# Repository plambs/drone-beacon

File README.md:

# Drone beacon

## Description

This repository contain the source code and schematic of the drone beacon that is mandatory for all flying models over 800gr in France.
The beacon use a ESP32 to send the model id over wifi and a gps module to know it position.

All model must be registered on [AlphaTango](https://alphatango.aviation-civile.gouv.fr/login.jsp)

This work is based on the work done by Arnaud Mazin and the source of it can be found [here](https://www.club-modelisme-saclay.fr/ameliorations-balise-signalement-electronique-modeles-reduits-volants/)

## Build, flash and monitor

### Install ESP-IDF tools

Follow the [get-started](https://docs.espressif.com/projects/esp-idf/en/stable/esp32/get-started/linux-macos-setup.html) of the ESP IDF tools documentation.

For linux users
```
sudo apt-get install git wget flex bison gperf python3 python3-pip python3-venv cmake ninja-build ccache libffi-dev libssl-dev dfu-util libusb-1.0-0

mkdir -p ~/esp
cd ~/esp
git clone -b v5.4.3 --recursive https://github.com/espressif/esp-idf.git

cd ~/esp/esp-idf
./install.sh esp32
```

After that when you want to use the ESP-IDF tools you only need to source the export.sh script.
```
. $HOME/esp/esp-idf/export.sh
```

### Init submodule

```
git submodule update --init --recursive
```

### Beacon

```
cd sources/beacon
idf.py build
idf.py flash
```

Balise status code
|Status|Fast blink|Slow blink|
|---|---|---|
|Reset GPS|4||
|No position|3||
|Position but no home (not enough precision)|2||
|Trasmiting beacon (beacon is working)||1|

Initialisation time take at least 2 minute in ideal condition

### Receiver

```
cd sources/receiver
idf.py build
idf.py flash
```

### Monitor the serial output

```
idf.py monitor
```
To exit the monitor use Ctrl+T Ctrl+X

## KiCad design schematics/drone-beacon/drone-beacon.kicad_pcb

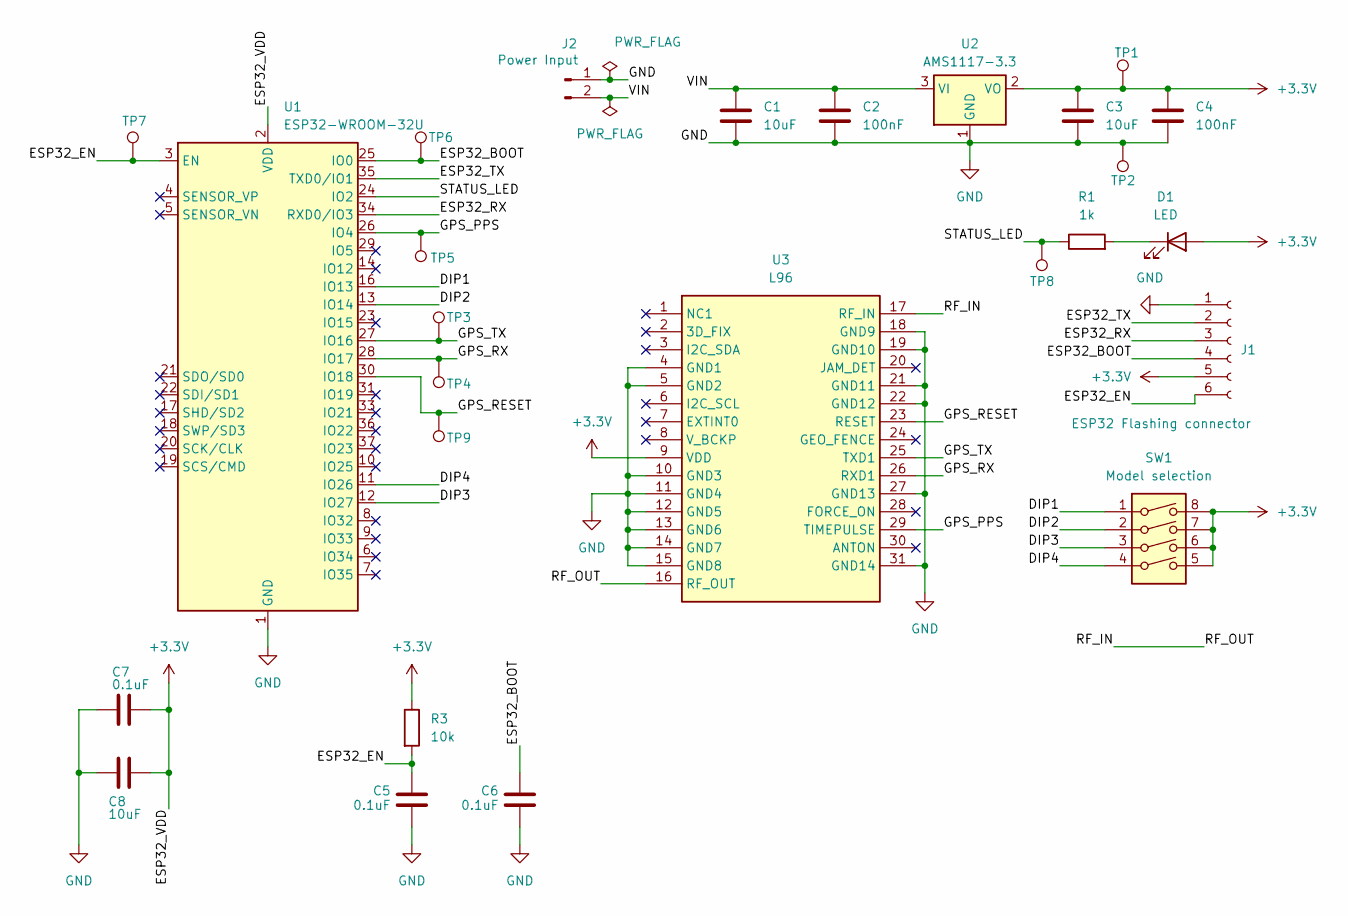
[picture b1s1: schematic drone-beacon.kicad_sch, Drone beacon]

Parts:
C1, C3, C8: 10uF; C_0402_1005Metric_Pad0.74x0.62mm_HandSolder
C2, C4: 100nF; C_0402_1005Metric_Pad0.74x0.62mm_HandSolder
C5, C6, C7: 0.1uF; C_0402_1005Metric_Pad0.74x0.62mm_HandSolder
D1: LED; LED_0402_1005Metric_Pad0.77x0.64mm_HandSolder
J1: ESP32 Flashing connector; JST_SHL_SM06B-SHLS-TF_1x06-1MP_P1.00mm_Horizontal
J2: Power Input; PinHeader_1x02_P2.00mm_Vertical
R1: 1k; R_0402_1005Metric_Pad0.72x0.64mm_HandSolder
R3: 10k; R_0402_1005Metric_Pad0.72x0.64mm_HandSolder
SW1: Model selection; SW_DIP_SPSTx04_Slide_Copal_CHS-04B_W7.62mm_P1.27mm
TP1, TP2, TP3, TP4, TP5, TP6, TP7, TP8, TP9: TestPoint; TestPoint_Pad_D1.0mm
U1: ESP32-WROOM-32U
U2: AMS1117-3.3; SOT-223
U3: L96; Quectel_L96; Mouser Part Number 277-L96-M33

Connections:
+3.3V: C3.1, C4.1, C7.1, C8.1, D1.2 (A), J1.5, R3.1, SW1.5, SW1.6, SW1.7, SW1.8, TP1.1, U1.2 (VDD), U2.2 (VO), U3.9 (VDD)
/DIP1: SW1.1, U1.16 (IO13)
/DIP2: SW1.2, U1.13 (IO14)
/DIP3: SW1.3, U1.12 (IO27)
/DIP4: SW1.4, U1.11 (IO26)
/ESP32_BOOT: C6.1, J1.4, TP6.1, U1.25 (IO0)
/ESP32_EN: C5.1, J1.6, R3.2, TP7.1, U1.3 (EN)
/ESP32_RX: J1.3, U1.34 (RXD0/IO3)
/ESP32_TX: J1.2, U1.35 (TXD0/IO1)
/GPS_PPS: TP5.1, U1.26 (IO4), U3.29 (TIMEPULSE)
/GPS_RESET: TP9.1, U1.30 (IO18), U3.23 (RESET)
/GPS_RX: TP4.1, U1.28 (IO17), U3.26 (RXD1)
/GPS_TX: TP3.1, U1.27 (IO16), U3.25 (TXD1)
/RF_IN: U3.16 (RF_OUT), U3.17 (RF_IN)
/STATUS_LED: R1.1, TP8.1, U1.24 (IO2)
/VIN: C1.1, C2.1, J2.2, U2.3 (VI)
GND: C1.2, C2.2, C3.2, C4.2, C5.2, C6.2, C7.2, C8.2, J1.1, J2.1, TP2.1, U1.1 (GND), U1.15 (GND), U1.38 (GND), U1.39 (GND), U2.1 (GND), U3.4 (GND1), U3.5 (GND2), U3.10 (GND3), U3.11 (GND4), U3.12 (GND5), U3.13 (GND6), U3.14 (GND7), U3.15 (GND8), U3.18 (GND9), U3.19 (GND10), U3.21 (GND11), U3.22 (GND12), U3.27 (GND13), U3.31 (GND14)
unnamed: D1.1 (K), R1.2

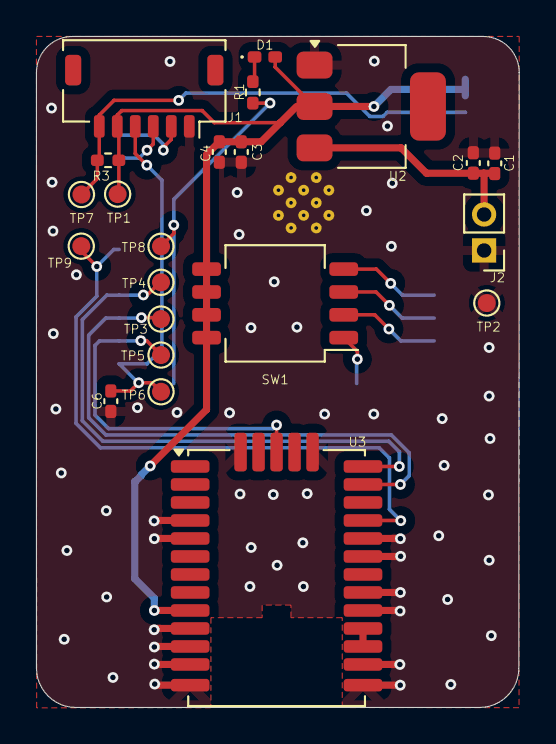
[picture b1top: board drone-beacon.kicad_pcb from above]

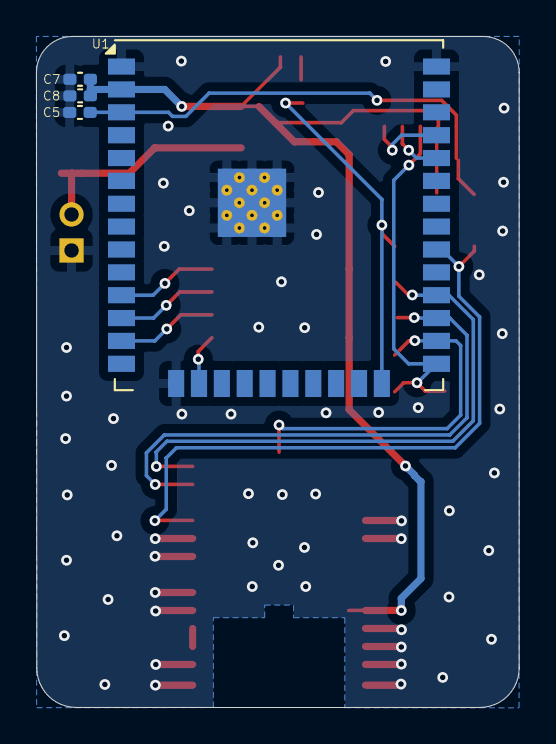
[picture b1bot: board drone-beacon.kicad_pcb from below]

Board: 2 copper layers, 26.8 x 37.3 mm, 26 parts (4 on the bottom side), 18 nets.

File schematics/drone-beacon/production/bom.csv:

Designator,Footprint,Quantity,Value,LCSC Part #
"C1, C3, C8",0402,3,10uF,
"C2, C4",0402,2,100nF,
"C5, C6, C7",0402,3,0.1uF,
D1,0402,1,LED,
J1,JST_SHL_SM06B-SHLS-TF_1x06-1MP_P1.00mm_Horizontal,1,ESP32 Flashing connector,
J2,PinHeader_1x02_P2.00mm_Vertical,1,Power Input,
R1,0402,1,1k,
R3,0402,1,10k,
SW1,SW_DIP_SPSTx04_Slide_Copal_CHS-04B_W7.62mm_P1.27mm,1,Model selection,
"TP1, TP2, TP3, TP4, TP5, TP6, TP7, TP8, TP9",TestPoint_Pad_D1.0mm,9,TestPoint,
U1,ESP32-WROOM-32U,1,ESP32-WROOM-32U,
U2,SOT-223,1,AMS1117-3.3,
U3,Quectel_L96,1,L96,

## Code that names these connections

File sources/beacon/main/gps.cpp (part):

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#define GPS_BAUDRATE_CHANGE_DELAY_MS  600
#define GPS_BAUDRATE_DEFAULT         9600
#define GPS_BAUDRATE_115200        115200
#define GPS_RX_PIN                     16
#define GPS_TX_PIN                     17
#define GPS_RESET_PIN           GPIO_NUM_18

static TinyGPSPlus gps;
static bool has_set_home = false;
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	}
	fail_if_not_zero(ret, -2, "uart_param_config failed, returned: %d\n", ret);

	ret = uart_set_pin(UART_NUM_2, GPS_TX_PIN, GPS_RX_PIN, UART_PIN_NO_CHANGE, UART_PIN_NO_CHANGE);
	fail_if_not_zero(ret, -3, "uart_set_pin failed, returned: %d\n", ret);

	// Flush the uart2 rx buffer to start with a fresh empty buffer.
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
	log_info("Trigger GPS module reset\n");

	ret = gpio_set_level(GPS_RESET_PIN, 0);
	fail_if_not_zero(ret, -1, "gpio_set_level(0) failed, returned: %d\n", ret);

	vTaskDelay(pdMS_TO_TICKS(GPS_RESET_TRIGGER_DELAY_MS));

	ret = gpio_set_level(GPS_RESET_PIN, 1);
	fail_if_not_zero(ret, -2, "gpio_set_level(1) failed, returned: %d\n", ret);

	vTaskDelay(pdMS_TO_TICKS(GPS_RESET_TRIGGER_DELAY_MS));
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
	// Init the gps module is nothing more than setting the reset
	// gpio as output and launching the gps reset sequence.
	ret = gpio_set_direction(GPS_RESET_PIN, GPIO_MODE_OUTPUT);
	fail_if_not_zero(ret, -1, "gpio_set_direction failed, returned: %d\n", ret);

	ret = gpio_set_level(GPS_RESET_PIN, 1);
	fail_if_not_zero(ret, -2, "gpio_set_level failed, returned: %d\n", ret);

	vTaskDelay(pdMS_TO_TICKS(200));
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
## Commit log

2025-03-09 Make the beacon source build with esp-idf toolchain
2025-03-09 Add TinyGPSPlus and droneID_FR components sources
2025-03-09 Rework receiver folder shape (WIP)
2025-03-12 Add lvgl components for receiver
2025-03-12 Add kicad schematics for the drone-beacon
2025-03-13 Update schematics
2025-03-13 Publish pcb production files
2025-03-13 Add BOM in documentation
2025-04-06 Update beacon application (WIP)
2025-04-06 Update receiver sources (WIP)
2025-04-06 Update schematics (WIP)
2025-04-12 Update beacon sources (WIP)
2025-10-14 Update schematics v1
2025-10-14 Add documentation
2025-10-26 Fix build with esp-idf v5.4.3
2026-04-12 Fix some gps configuration issues
2026-04-12 dos2unix main_app.cpp
2026-04-12 Cleanup and replace Serial.print* by printf
2026-04-12 Print all sentence received and manually parse *GSV one
2026-05-03 Use define to enable/disable debug logs, cleanup some printf
2026-05-04 dos2unix receiver main_app.cpp
2026-05-04 fix receiver build using esp-idf v5.4
2026-05-04 beacon: reduce loop delay from 100ms to 10ms
2026-05-14 Update logs
2026-05-16 move led management in its own source file
2026-06-01 beacon: refacto, split sources in specific functions files
2026-06-01 schematics: update schematics and add missing pull up/down
2026-06-01 beacon: enable sleep mode
2026-06-01 beacon: update satellites in view debug information
2026-06-11 beacon: replace most of arduino code by esp-idf one
2026-06-27 beacon: improve gps management and configuration
2026-06-27 beacon: add logging capabilities
2026-06-27 beacon: check most of the function parameter and return value
2026-06-27 beacon: replace printf by log_*
2026-06-27 beacon: change gps timming and flush uart at init
2026-06-27 beacon: set defaut log level at INFO
2026-06-28 doc: add esp32 wroom32 datasheet
2026-06-28 chore: cleanup documentation folder
2026-06-28 schematic: update capacitor values
2026-06-28 beacon: fix group and mass dipswitch value computation
